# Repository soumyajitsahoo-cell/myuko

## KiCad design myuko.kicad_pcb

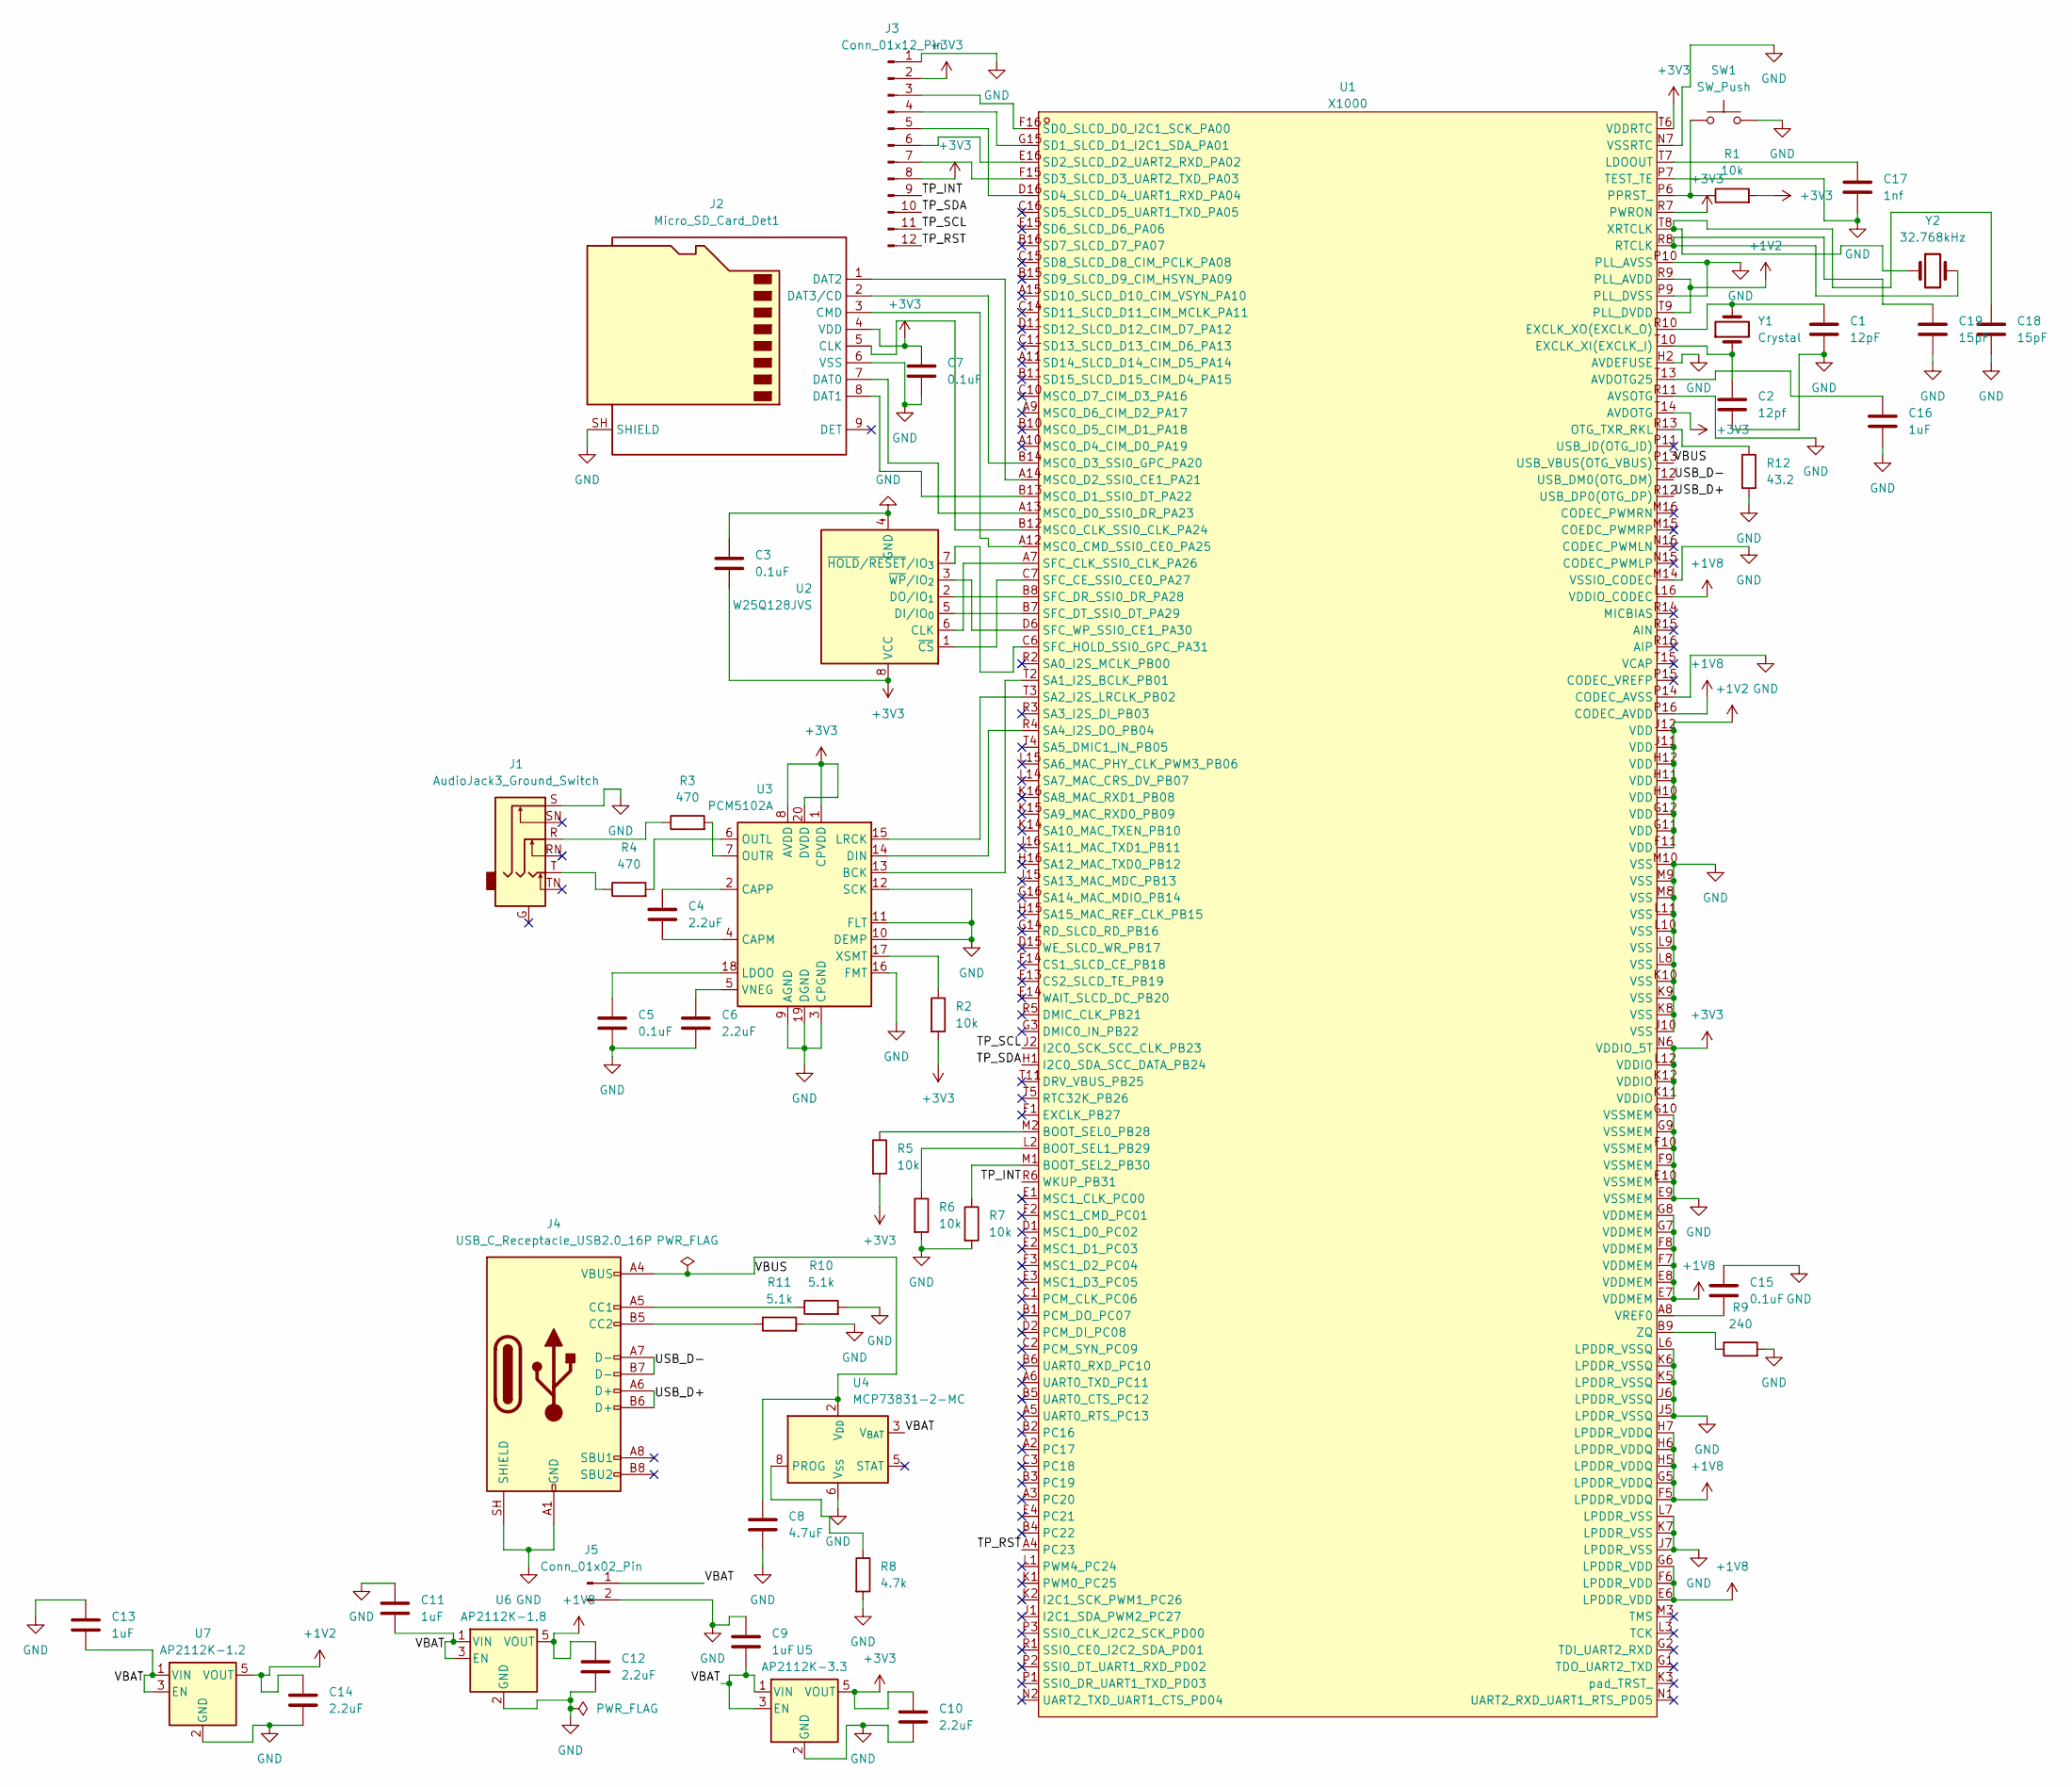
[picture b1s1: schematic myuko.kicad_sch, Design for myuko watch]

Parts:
C1: 12pF; C_0402_1005Metric
C2: 12pf; C_0402_1005Metric
C3, C5, C7, C15: 0.1uF; C_0402_1005Metric
C4, C6, C10, C12, C14: 2.2uF; C_0402_1005Metric
C8: 4.7uF; C_0402_1005Metric
C9, C11, C13, C16: 1uF; C_0402_1005Metric
C17: 1nf; C_0402_1005Metric
C18, C19: 15pF; C_0402_1005Metric
J1: AudioJack3_Ground_Switch; Jack_3.5mm_CUI_SJ-3523-SMT_Horizontal
J2: Micro_SD_Card_Det1; microSD_HC_Hirose_DM3D-SF
J3: Conn_01x12_Pin; Hirose_FH12-12S-0.5SH_1x12-1MP_P0.50mm_Horizontal
J4: USB_C_Receptacle_USB2.0_16P; USB_C_Receptacle_HCTL_HC-TYPE-C-16P-01A
J5: Conn_01x02_Pin; JST_PH_S2B-PH-K_1x02_P2.00mm_Horizontal
R1, R2, R5, R6, R7: 10k; R_0402_1005Metric
R3, R4: 470; R_0402_1005Metric
R8: 4.7k; R_0402_1005Metric
R9: 240; R_0402_1005Metric
R10, R11: 5.1k; R_0402_1005Metric
R12: 43.2; R_0402_1005Metric
SW1: SW_Push; SW_Push_1P1T_NO_CK_KMR2
U1: X1000; BGA-190_L13.0-W13.0-R16-C16-P0.8-TR; MPN X1000; LCSC Part C2689394
U2: W25Q128JVS; SOIC-8_5.3x5.3mm_P1.27mm
U3: PCM5102A; TSSOP-20_4.4x6.5mm_P0.65mm
U4: MCP73831-2-MC; DFN-8-1EP_3x2mm_P0.5mm_EP1.7x1.4mm
U5: AP2112K-3.3; SOT-23-5
U6: AP2112K-1.8; SOT-23-5
U7: AP2112K-1.2; SOT-23-5
Y1: Crystal; Crystal_SMD_3225-4Pin_3.2x2.5mm
Y2: 32.768kHz; Crystal_SMD_3215-2Pin_3.2x1.5mm

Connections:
+1V2: C14.1, U1.F11 (VDD), U1.G11 (VDD), U1.G12 (VDD), U1.H10 (VDD), U1.H11 (VDD), U1.H12 (VDD), U1.J11 (VDD), U1.J12 (VDD), U1.R9 (PLL_AVDD), U1.T9 (PLL_DVDD), U7.5 (VOUT)
+1V8: C12.1, U1.E6 (LPDDR_VDD), U1.E7 (VDDMEM), U1.E8 (VDDMEM), U1.F5 (LPDDR_VDDQ), U1.F6 (LPDDR_VDD), U1.F7 (VDDMEM), U1.F8 (VDDMEM), U1.G5 (LPDDR_VDDQ), U1.G6 (LPDDR_VDD), U1.G7 (VDDMEM), U1.G8 (VDDMEM), U1.H5 (LPDDR_VDDQ), U1.H6 (LPDDR_VDDQ), U1.H7 (LPDDR_VDDQ), U1.L16 (VDDIO_CODEC), U1.P16 (CODEC_AVDD), U6.5 (VOUT)
+3V3: C3.1, C7.1, C10.1, J2.4 (VDD), J3.2, J3.8, R1.2, R2.2, R5.2, U1.K11 (VDDIO), U1.K12 (VDDIO), U1.L12 (VDDIO), U1.N6 (VDDIO_5T), U1.R7 (PWRON), U1.T6 (VDDRTC), U1.T14 (AVDOTG), U2.8 (VCC), U3.1 (CPVDD), U3.8 (AVDD), U3.20 (DVDD), U5.5 (VOUT)
/TP_INT: J3.9, U1.R6 (WKUP_PB31)
/TP_RST: J3.12, U1.A4 (PC23)
/TP_SCL: J3.11, U1.J2 (I2C0_SCK_SCC_CLK_PB23)
/TP_SDA: J3.10, U1.H1 (I2C0_SDA_SCC_DATA_PB24)
/USB_D+: J4.A6 (D+), J4.B6 (D+), U1.R12 (USB_DP0(OTG_DP))
/USB_D-: J4.A7 (D-), J4.B7 (D-), U1.T12 (USB_DM0(OTG_DM))
/VBAT: C9.2, C11.2, C13.2, J5.1, U4.3 (V_{BAT}), U4.4 (V_{BAT}), U5.1 (VIN), U5.3 (EN), U6.1 (VIN), U6.3 (EN), U7.1 (VIN), U7.3 (EN)
/VBUS: C8.1, J4.A4 (VBUS), J4.A9 (VBUS), J4.B4 (VBUS), J4.B9 (VBUS), U1.P13 (USB_VBUS(OTG_VBUS)), U4.1 (V_{DD}), U4.2 (V_{DD})
GND: C1.2, C2.2, C3.2, C5.2, C6.2, C7.2, C8.2, C9.1, C10.2, C11.1, C12.2, C13.1, C14.2, C15.1, C16.2, C17.2, C18.2, C19.2, J1.S, J2.6 (VSS), J2.SH (SHIELD), J3.1, J4.A1 (GND), J4.A12 (GND), J4.B1 (GND), J4.B12 (GND), J4.SH (SHIELD), J5.2, R6.2, R7.2, R8.2, R9.2, R10.2, R11.2, R12.2, SW1.2, U1.E9 (VSSMEM), U1.E10 (VSSMEM), U1.F9 (VSSMEM), U1.F10 (VSSMEM), U1.G9 (VSSMEM), U1.G10 (VSSMEM), U1.H2 (AVDEFUSE), U1.J5 (LPDDR_VSSQ), U1.J6 (LPDDR_VSSQ), U1.J7 (LPDDR_VSS), U1.J10 (VSS), U1.K5 (LPDDR_VSSQ), U1.K6 (LPDDR_VSSQ), U1.K7 (LPDDR_VSS), U1.K8 (VSS), U1.K9 (VSS), U1.K10 (VSS), U1.L6 (LPDDR_VSSQ), U1.L7 (LPDDR_VSS), U1.L8 (VSS), U1.L9 (VSS), U1.L10 (VSS), U1.L11 (VSS), U1.M8 (VSS), U1.M9 (VSS), U1.M10 (VSS), U1.M14 (VSSIO_CODEC), U1.N7 (VSSRTC), U1.P7 (TEST_TE), U1.P9 (PLL_DVSS), U1.P10 (PLL_AVSS), U1.P14 (CODEC_AVSS), U1.R11 (AVSOTG), U2.4 (GND), U3.3 (CPGND), U3.9 (AGND), U3.10 (DEMP), U3.11 (FLT), U3.12 (SCK), U3.16 (FMT), U3.19 (DGND), U4.6 (V_{SS}), U5.2 (GND), U6.2 (GND), U7.2 (GND)
unnamed: J1.R, R3.1
unnamed: J1.T, R4.1
unnamed: J2.5 (CLK), U1.B12 (MSC0_CLK_SSI0_CLK_PA24)
unnamed: J2.3 (CMD), U1.A12 (MSC0_CMD_SSI0_CE0_PA25)
unnamed: J2.7 (DAT0), U1.A13 (MSC0_D0_SSI0_DR_PA23)
unnamed: J2.8 (DAT1), U1.B13 (MSC0_D1_SSI0_DT_PA22)
unnamed: J2.1 (DAT2), U1.A14 (MSC0_D2_SSI0_CE1_PA21)
unnamed: J2.2 (DAT3/CD), U1.B14 (MSC0_D3_SSI0_GPC_PA20)
unnamed: J3.3, U1.F16 (SD0_SLCD_D0_I2C1_SCK_PA00)
unnamed: J3.4, U1.G15 (SD1_SLCD_D1_I2C1_SDA_PA01)
unnamed: J3.5, U1.D16 (SD4_SLCD_D4_UART1_RXD_PA04)
unnamed: J3.6, U1.E16 (SD2_SLCD_D2_UART2_RXD_PA02)
unnamed: J3.7, U1.F15 (SD3_SLCD_D3_UART2_TXD_PA03)
unnamed: J4.A5 (CC1), R10.1
unnamed: J4.B5 (CC2), R11.1
unnamed: C16.1, U1.T13 (AVDOTG25)
unnamed: R5.1, U1.M2 (BOOT_SEL0_PB28)
unnamed: R6.1, U1.L2 (BOOT_SEL1_PB29)
unnamed: R7.1, U1.M1 (BOOT_SEL2_PB30)
unnamed: C2.1, U1.T10 (EXCLK_XI(EXCLK_I)), Y1.1
unnamed: C1.1, U1.R10 (EXCLK_XO(EXCLK_O)), Y1.2
unnamed: C17.1, U1.T7 (LDOOUT)
unnamed: R12.1, U1.R13 (OTG_TXR_RKL)
unnamed: R1.1, SW1.1, U1.P6 (PPRST_)
unnamed: C19.1, U1.R8 (RTCLK), Y2.2
unnamed: U1.T2 (SA1_I2S_BCLK_PB01), U3.13 (BCK)
unnamed: U1.T3 (SA2_I2S_LRCLK_PB02), U3.15 (LRCK)
unnamed: U1.R4 (SA4_I2S_DO_PB04), U3.14 (DIN)
unnamed: U1.C7 (SFC_CE_SSI0_CE0_PA27), U2.1 (~CS)
unnamed: U1.A7 (SFC_CLK_SSI0_CLK_PA26), U2.6 (CLK)
unnamed: U1.B8 (SFC_DR_SSI0_DR_PA28), U2.2 (DO/IO_{1})
unnamed: U1.B7 (SFC_DT_SSI0_DT_PA29), U2.5 (DI/IO_{0})
unnamed: U1.C6 (SFC_HOLD_SSI0_GPC_PA31), U2.7 (~HOLD/~RESET/IO_{3})
unnamed: U1.D6 (SFC_WP_SSI0_CE1_PA30), U2.3 (~WP/IO_{2})
unnamed: C15.2, U1.A8 (VREF0)
unnamed: C18.1, U1.T8 (XRTCLK), Y2.1
unnamed: R9.1, U1.B9 (ZQ)
unnamed: C4.2, U3.4 (CAPM)
unnamed: C4.1, U3.2 (CAPP)
unnamed: C5.1, U3.18 (LDOO)
unnamed: R4.2, U3.6 (OUTL)
unnamed: R3.2, U3.7 (OUTR)
unnamed: C6.1, U3.5 (VNEG)
unnamed: R2.1, U3.17 (XSMT)
unnamed: R8.1, U4.8 (PROG)

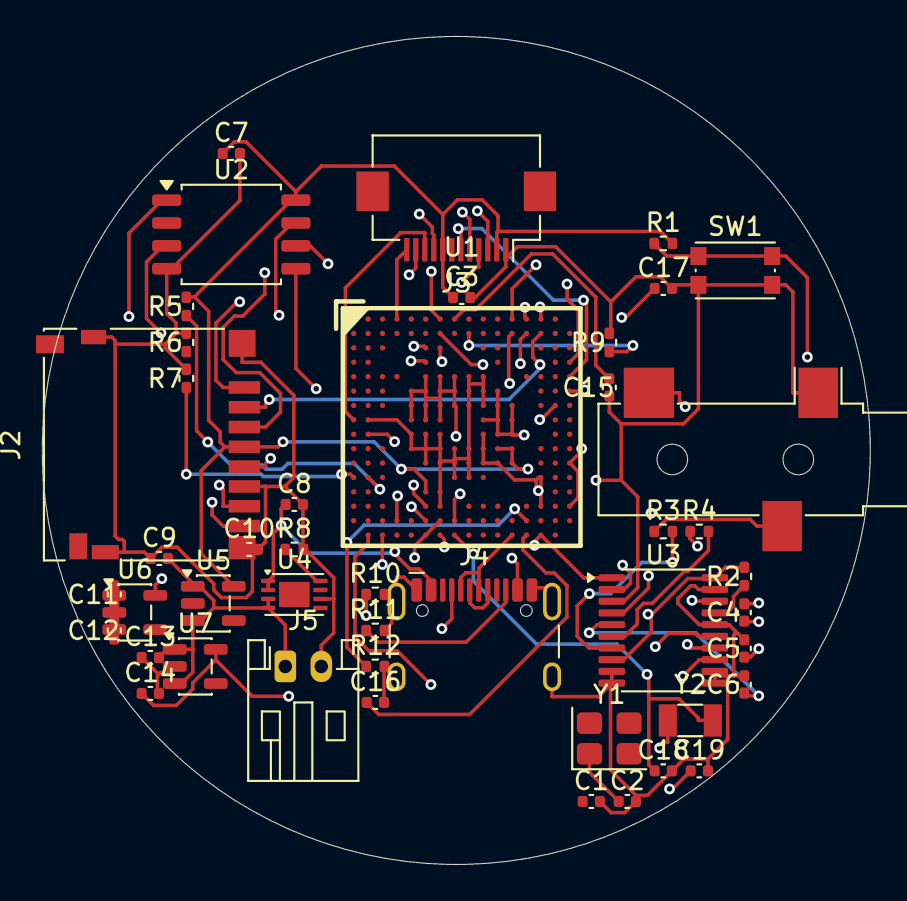
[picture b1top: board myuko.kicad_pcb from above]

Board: 4 copper layers, 46.0 x 46.0 mm, 46 parts (0 on the bottom side), 57 nets.

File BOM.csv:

Part,Type,Quantity,Unit price (USD),Line total (USD),Link,Vendor,Funding,Notes,Designator,Footprint,LCSC Part #
Ingenic X1000E MIPS32 1GHz SoC (64MB LPDDR),Part,1,5.80,5.80,https://www.lcsc.com/product-detail/Microcontroller-Units-MC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,,Grant,,U1,BGA-190,C2689394
Winbond 16MB SPI NOR Flash (W25Q128JVS),Part,1,0.85,0.85,https://www.lcsc.com/product-detail/NOR-FLASH_Winbond-Elec-W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,,Grant,,U2,SOIC-8,C97521
TI PCM5102APWR 32-bit 384kHz Hi-Fi Audio DAC,Part,1,2.10,2.10,https://www.lcsc.com/product-detail/Audio-Power-OpAmps_Texas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,,Grant,,U3,TSSOP-20,C107671
Microchip MCP73831T Li-Po Charge Controller,Part,1,0.35,0.35,https://www.lcsc.com/product-detail/Battery-Management-ICs_M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,,Grant,,U4,DFN-8,C49774
AP2112K-3.3TRG1 3.3V 600mA Low Dropout Regulator,Part,1,0.18,0.18,https://www.lcsc.com/product-detail/Linear-Voltage-Regulator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,,Grant,,U5,SOT-23-5,C51118
AP2112K-1.8TRG1 1.8V 600mA Low Dropout Regulator,Part,1,0.18,0.18,https://www.lcsc.com/product-detail/Linear-Voltage-Regulator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,,Grant,,U6,SOT-23-5,C176944
AP2112K-1.2TRG1 1.2V 600mA Low Dropout Regulator,Part,1,0.32,0.32,https://www.lcsc.com/product-detail/Linear-Voltage-Regulator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,,Grant,,U7,SOT-23-5,C460310
24.000MHz +/-10ppm 12pF SMD Crystal,Part,1,0.12,0.12,https://www.lcsc.com/product-detail/Crystals_YXC-Yangxing-Te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,,Grant,,Y1,SMD-3225-4P,C70590
32.768kHz +/-20ppm 12.5pF RTC Sleep Crystal,Part,1,0.15,0.15,https://www.lcsc.com/product-detail/Crystals_Seiko-Epson-Q13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,,Grant,,Y2,SMD-3215-2P,C32346
3.5mm Stereo Audio Jack (SJ-3523-SMT),Part,1,0.25,0.25,https://www.lcsc.com/product-detail/Audio-Connectors_CUI-Dev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,,Grant,,J1,SMD-Horizontal,C4991872
MicroSD Push-Push Card Socket,Part,1,0.22,0.22,https://www.lcsc.com/product-detail/MicroSD-Card-Connectors_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,,Grant,,J2,SMD-Push-Push,C381082
0.5mm Pitch 12-Pin Flip-Lock FPC Display Connector,Part,1,0.10,0.10,https://www.lcsc.com/product-detail/FFC-FPC-Connectors_JUSHU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,,Grant,,J3,SMD-0.5mm,C262661
USB Type-C 16-Pin Receptacle,Part,1,0.12,0.12,https://www.lcsc.com/product-detail/USB-Connectors_HOO-R-TYP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,,Grant,,J4,SMD-TYPE-C-16P,C2765186
JST-PH 2.0mm 2-Pin Battery Plug,Part,1,0.05,0.05,https://www.lcsc.com/product-detail/Pluggable-System-Termina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,,Grant,,J5,SMD-JST-PH-2P,C131337
Tactile Push Button SMD (KMR2),Part,1,0.04,0.04,https://www.lcsc.com/product-detail/Tactile-Switches_SHOU-HA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,,Grant,,SW1,SMD-4.2x2.8mm,C318884
12pF 50V C0G 0402 Capacitor,Part,2,0.005,0.01,https://www.lcsc.com/product-detail/Multilayer-Ceramic-Capac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,,Grant,,"C1, C2",0402,C1547
0.1uF (100nF) 16V X7R 0402 Decoupling Capacitor,Part,4,0.005,0.02,https://www.lcsc.com/product-detail/Multilayer-Ceramic-Capac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,,Grant,,"C3, C5, C7, C15",0402,C1525
2.2uF 10V X5R 0402 Capacitor,Part,5,0.008,0.04,https://www.lcsc.com/product-detail/Multilayer-Ceramic-Capac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,,Grant,,"C4, C6, C10, C12, C14",0402,C23630
4.7uF 10V X5R 0402 Capacitor,Part,1,0.01,0.01,https://www.lcsc.com/product-detail/Multilayer-Ceramic-Capac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,,Grant,,C8,0402,C23633
1.0uF 16V X5R 0402 Capacitor,Part,4,0.006,0.02,https://www.lcsc.com/product-detail/Multilayer-Ceramic-Capac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,,Grant,,"C9, C11, C13, C16",0402,C52923
1.0nF 50V X7R 0402 Capacitor,Part,1,0.005,0.01,https://www.lcsc.com/product-detail/Multilayer-Ceramic-Capac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,,Grant,,C17,0402,C1523
15pF 50V C0G 0402 Capacitor,Part,2,0.005,0.01,https://www.lcsc.com/product-detail/Multilayer-Ceramic-Capac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,,Grant,,"C18, C19",0402,C1550
10k 1% 0402 Resistor,Part,5,0.003,0.01,https://www.lcsc.com/product-detail/Chip-Resistor-Surface-Mo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,,Grant,,"R1, R2, R5, R6, R7",0402,C25744
470R 1% 0402 Resistor,Part,2,0.003,0.01,https://www.lcsc.com/product-detail/Chip-Resistor-Surface-Mo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,,Grant,,"R3, R4",0402,C25117
4.7k 1% 0402 Resistor,Part,1,0.003,0.00,https://www.lcsc.com/product-detail/Chip-Resistor-Surface-Mo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,,Grant,,R8,0402,C25900
240R 1% 0402 Resistor,Part,1,0.003,0.00,https://www.lcsc.com/product-detail/Chip-Resistor-Surface-Mo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,,Grant,,R9,0402,C25091
5.1k 1% 0402 Resistor (USB-C CC Pull-down),Part,2,0.003,0.01,https://www.lcsc.com/product-detail/Chip-Resistor-Surface-Mo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,,Grant,,"R10, R11",0402,C25905
43.2R 1% 0402 Resistor (USB OTG bias),Part,1,0.003,0.00,https://www.lcsc.com/product-detail/Chip-Resistor-Surface-Mo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,,Grant,,R12,0402,C25121
"1.28-inch Circular 240x240 IPS Touchscreen Display (GC9A01 + CST816S, 12-pin FPC)",Part,1,4.80,4.80,https://www.waveshare.com/1.28inch-touch-lcd.htm,,Grant,,DISP1,1.28-inch Round Module,N/A (Waveshare / AliExpress)
3.7V 400mAh-500mAh Li-Po Rechargeable Battery (JST-PH 2.0),Part,1,3.50,3.50,https://www.adafruit.com/product/1578,,Grant,,BAT1,502530 Pouch (25x30x5mm),N/A (Adafruit / Makerfabs)
20mm Quick-Release Silicone Sports Watch Band,Part,1,2.50,2.50,https://www.amazon.com/dp/B07F2BF25S,,Grant,,STRAP1,20mm Lug Mount,N/A (Amazon / Retail)
"Custom 4-Layer Circular PCB Fabrication Batch (JLCPCB 5pcs, JLC04161H)",PCB,5,2.00,10.00,https://jlcpcb.com,,Grant,,PCB,Dia 46.0mm Circle 4-Layer FR4,JLCPCB PCB Order
Total,,,,31.78,,,,,,,
